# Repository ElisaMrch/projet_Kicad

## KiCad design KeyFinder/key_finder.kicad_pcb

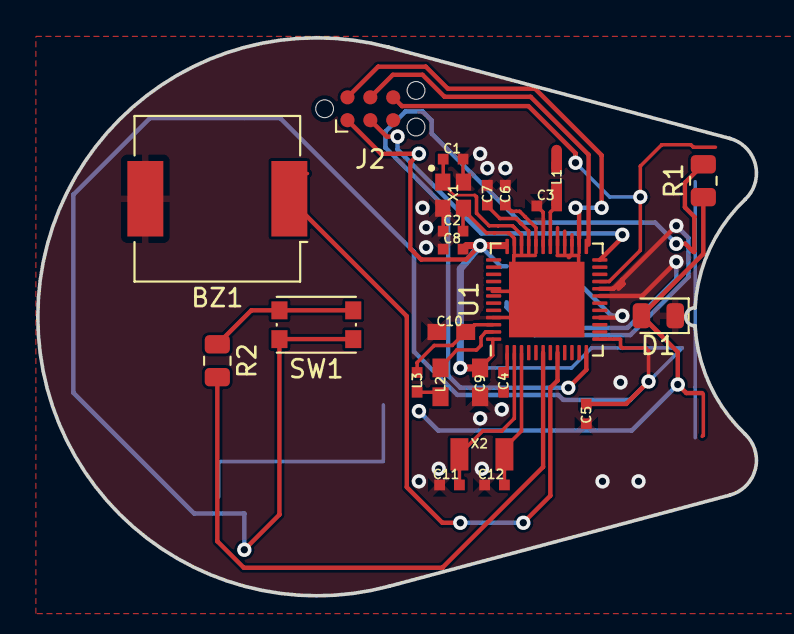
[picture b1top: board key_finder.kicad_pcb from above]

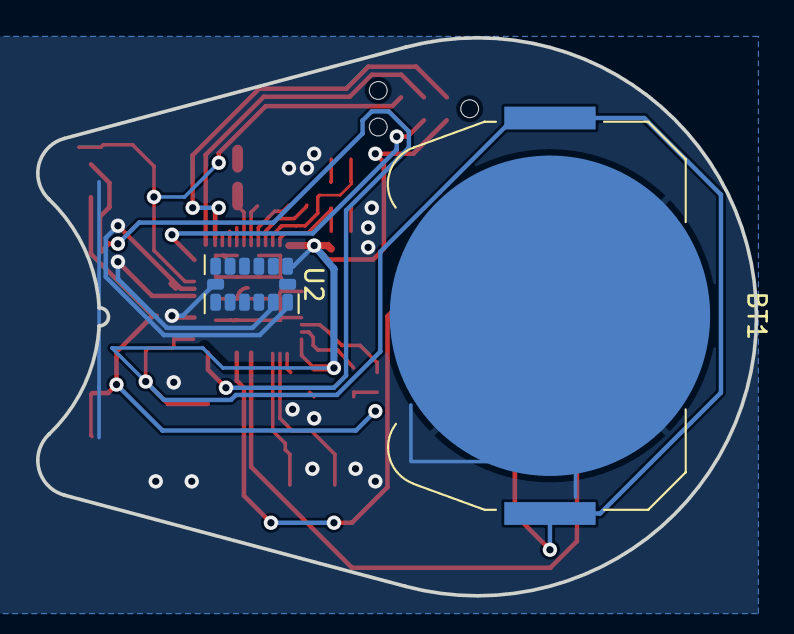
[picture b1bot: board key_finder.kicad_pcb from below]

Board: 2 copper layers, 39.9 x 31.0 mm, 26 parts (2 on the bottom side), 22 nets.

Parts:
BT1: Battery; BatteryHolder_Keystone_3034_1x20mm
BZ1: Buzzer; Buzzer_CUI_CPT-9019S-SMT
C1, C2, C11, C12: 12pF; RESC0402_N
C3: 0.8pF; RESC0402_N
C4, C5, C8: 100nF; RESC0402_N
C6: N.M.; RESC0402_N
C7: 100pF; RESC0402_N
C9: 4.7µF; RESC0603_N
C10: 1.0µF; RESC0603_N
D1: LED; LED_0805_2012Metric
J2: Conn_ARM_SWD_TagConnect_TC2030-NL; Tag-Connect_TC2030-IDC-NL_2x03_P1.27mm_Vertical
L1: 3.9nH; RESC0402_N
L2: 10µH; RESC0603_N
L3: 15nH; RESC0402_N
R1: 330; R_0805_2012Metric
R2: 10k; R_0805_2012Metric
SW1: SW_Push; SW_Push_1P1T_NO_CK_KMR2
U1: NRF52832; QFN-48-1EP_6x6mm_P0.4mm_EP4.2x4.2mm
U2: ADXL343; LGA-14_3x5mm_P0.8mm_LayoutBorder1x6y
X1: 32MHz; BT-XTAL_2016_N
X2: 32.768kHz; XTAL_3215_N

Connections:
/CS: U1.16 (P0.13@16), U2.7 (~CS)
/P0.04: R2.2, U1.6 (P0.04/AIN2@06)
/P0.06: BZ1.1 (-), U1.8 (P0.06@08)
/P0.10: R1.2, U1.12 (P0.10/NFC2@12)
/P0.18/SWO: J2.6 (SWO), U1.21 (P0.18/SWO@21)
/P0.21/RESET: J2.3 (~RESET), U1.24 (P0.21/RESET@24)
/SCL: U1.17 (P0.14@17), U2.14 (SCL/SCLK)
/SDA: U1.20 (P0.17@20), U2.13 (SDA/SDI/SDIO)
/SDO: U1.19 (P0.16@19), U2.12 (SDO/ADDR)
/SWDCLK: J2.4 (SWCLK), U1.25 (SWDCLK@25)
/SWDIO: J2.2 (SWDIO), U1.26 (SWDIO@26)
ANT: C3.1, L1.1
DEC4: C10.1, L3.2
GND: BT1.2 (-), BZ1.2 (+), C1.2, C2.2, C3.2, C4.2, C5.2, C6.2, C7.2, C8.2, C9.2, C10.2, C11.1, C12.1, D1.1 (K), J2.5 (GND), U1.31 (VSS@31), U1.45 (VSS@45), U2.2 (GND), U2.4 (GND), U2.5 (GND), X1.2, X1.4
unnamed: L2.2, L3.1
unnamed: C2.1, X1.3
unnamed: D1.2 (A), R1.1
unnamed: R2.1, SW1.2
P0.00/XL1: C11.2, X2.1
P0.01/XL2: C12.2, X2.2
VCC: BT1.1 (+), C5.1, C8.1, C9.1, J2.1 (VCC), SW1.1, U1.13 (VDD@13), U1.36 (VDD@36), U1.48 (VDD@48), U2.1 (Vdd_I/O)
X1: C1.1, X1.1

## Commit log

2023-12-11 Create test
    test
2023-12-11 ajout des éléments du projet et un read me
